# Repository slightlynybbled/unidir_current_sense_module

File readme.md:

# Unidirectional Current Sense Module #

This repository contains the schematic, layout, and gerber files to build a unidirectional current sensor breakout board.  More details can be found at [forembed](http://www.forembed.com/creating-the-current-sensor-board).

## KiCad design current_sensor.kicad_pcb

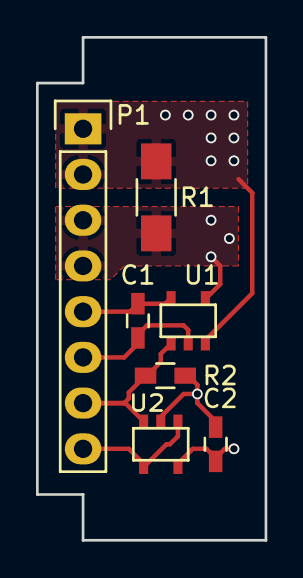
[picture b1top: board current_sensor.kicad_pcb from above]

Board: 2 copper layers, 12.7 x 27.9 mm, 7 parts (0 on the bottom side), 6 nets.

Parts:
C1, C2: 100nF; C_0603_HandSoldering
P1: CONN_01X08; Pin_Header_Straight_1x08
R1: 0.05; R_1206_HandSoldering
R2: 47k; R_0603_HandSoldering
U1: INA1x9_CURRENT_SENSOR_IC; SOT-23-5
U2: MCP6001; SOT-23-5

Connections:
GND: C1.2, C2.2, P1.6, R2.1, U1.2, U2.2
VCC: C1.1, C2.1, P1.5, U1.5, U2.5
Vbuf: P1.8, U2.1, U2.4
Vload: P1.3, P1.4, R1.1, U1.4
Vps: P1.1, P1.2, R1.2, U1.3
Vsense: P1.7, R2.2, U1.1, U2.3

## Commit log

2016-03-03 Added readme
2016-07-13 Added MIT license
